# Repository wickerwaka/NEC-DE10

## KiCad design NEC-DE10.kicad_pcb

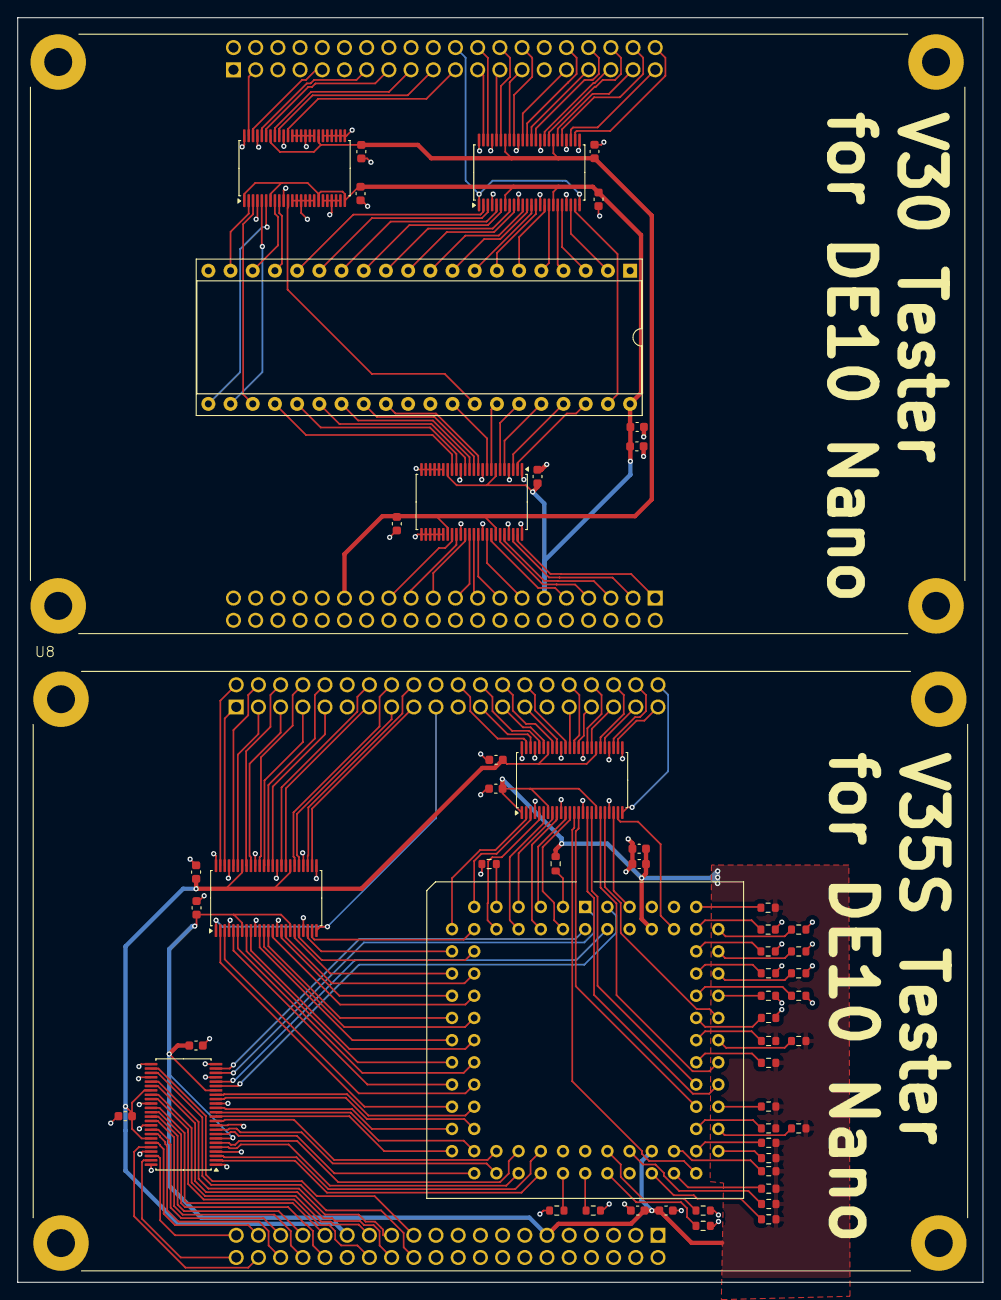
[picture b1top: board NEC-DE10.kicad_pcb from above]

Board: 2 copper layers, 110.4 x 144.7 mm, 56 parts (0 on the bottom side), 200 nets.

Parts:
C1, C2, C3, C4, C5, C6, C7, C8, C9, C10, C11, C12, C13, C14, C15: 100nF; C_0603_1608Metric
C16, C17, C18: 1uF; C_0603_1608Metric
R1, R2, R3, R4, R5, R6, R7, R8, R9, R10, R11, R12, R13, R14, R15, R16, R17, R18, R19, R20, R21, R22, R23, R24, R25, R26, R27, R28: 10k; R_0603_1608Metric
U1: DIP-40_W15.24mm_Socket
U2, U8: MODULE_P0496
U3, U4, U5, U6, U7, U10: 74ALVC164245; TSSOP-48_6.1x12.5mm_P0.5mm
U9: PLCC-84_THT-Socket

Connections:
+3.3V: C1.1, C2.1, C3.1, C8.1, C10.1, C12.1, U2.JP7_29 (3.3V_JP7), U3.31 (V_{CC(A)}), U3.42 (V_{CC(A)}), U4.31 (V_{CC(A)}), U4.42 (V_{CC(A)}), U5.31 (V_{CC(A)}), U5.42 (V_{CC(A)}), U6.31 (V_{CC(A)}), U6.42 (V_{CC(A)}), U7.31 (V_{CC(A)}), U7.42 (V_{CC(A)}), U8.JP7_29 (3.3V_JP7), U10.31 (V_{CC(A)}), U10.42 (V_{CC(A)})
+5V: C4.1, C5.1, C6.1, C7.1, C9.1, C11.1, C13.1, C14.1, C15.1, C16.1, C17.1, C18.1, R9.1, R10.1, R11.1, R12.1, R13.1, R14.1, R15.1, R16.1, R17.1, R18.1, R19.1, R25.1, R26.1, R27.1, U1.40 (VDD), U2.JP7_11 (5V_JP7), U3.7 (V_{CC(B)}), U3.18 (V_{CC(B)}), U4.7 (V_{CC(B)}), U4.18 (V_{CC(B)}), U5.1 (1DIR), U5.7 (V_{CC(B)}), U5.18 (V_{CC(B)}), U5.24 (2DIR), U6.7 (V_{CC(B)}), U6.18 (V_{CC(B)}), U7.7 (V_{CC(B)}), U7.18 (V_{CC(B)}), U8.JP7_11 (5V_JP7), U9.50 (VDD), U9.80 (VDD), U10.1 (1DIR), U10.7 (V_{CC(B)}), U10.18 (V_{CC(B)})
/V30/A16: U1.38 (A16/PS0), U4.2 (1B0)
/V30/A17: U1.37 (A17/PS1), U4.3 (1B1)
/V30/A18: U1.36 (A18/PS2), U4.5 (1B2)
/V30/A19: U1.35 (A19/PS3), U4.6 (1B3)
/V30/AD0: U1.16 (AD0), U3.2 (1B0)
/V30/AD1: U1.15 (AD1), U3.3 (1B1)
/V30/AD2: U1.14 (AD2), U3.5 (1B2)
/V30/AD3: U1.13 (AD3), U3.6 (1B3)
/V30/AD4: U1.12 (AD4), U3.8 (1B4)
/V30/AD5: U1.11 (AD5), U3.9 (1B5)
/V30/AD6: U1.10 (AD6), U3.11 (1B6)
/V30/AD7: U1.9 (AD7), U3.12 (1B7)
/V30/AD8: U1.8 (AD8), U3.13 (2B0)
/V30/AD9: U1.7 (AD9), U3.14 (2B1)
/V30/AD10: U1.6 (AD10), U3.16 (2B2)
/V30/AD11: U1.5 (AD11), U3.17 (2B3)
/V30/AD12: U1.4 (AD12), U3.19 (2B4)
/V30/AD13: U1.3 (AD13), U3.20 (2B5)
/V30/AD14: U1.2 (AD14), U3.22 (2B6)
/V30/AD15: U1.39 (AD15), U3.23 (2B7)
/V30/ASTB: U1.25 (ASTB), U4.16 (2B2)
/V30/BUF~R/W: U1.27 (BUF~R/W), U4.13 (2B0)
/V30/CLK: U1.19 (CLK), U5.2 (1B0)
/V30/F_A16: U2.JP7_1 (GPIO1_0), U4.47 (1A0)
/V30/F_A17: U2.JP7_3 (GPIO1_2), U4.46 (1A1)
/V30/F_A18: U2.JP7_5 (GPIO1_4), U4.44 (1A2)
/V30/F_A19: U2.JP7_7 (GPIO1_6), U4.43 (1A3)
/V30/F_AD0: U2.JP1_23 (GPIO0_20), U3.47 (1A0)
/V30/F_AD1: U2.JP1_24 (GPIO0_21), U3.46 (1A1)
/V30/F_AD2: U2.JP1_25 (GPIO0_22), U3.44 (1A2)
/V30/F_AD3: U2.JP1_26 (GPIO0_23), U3.43 (1A3)
/V30/F_AD4: U2.JP1_27 (GPIO0_24), U3.41 (1A4)
/V30/F_AD5: U2.JP1_28 (GPIO0_25), U3.40 (1A5)
/V30/F_AD6: U2.JP1_31 (GPIO0_26), U3.38 (1A6)
/V30/F_AD7: U2.JP1_32 (GPIO0_27), U3.37 (1A7)
/V30/F_AD8: U2.JP1_33 (GPIO0_28), U3.36 (2A0)
/V30/F_AD9: U2.JP1_34 (GPIO0_29), U3.35 (2A1)
/V30/F_AD10: U2.JP1_35 (GPIO0_30), U3.33 (2A2)
/V30/F_AD11: U2.JP1_36 (GPIO0_31), U3.32 (2A3)
/V30/F_AD12: U2.JP1_37 (GPIO0_32), U3.30 (2A4)
/V30/F_AD13: U2.JP1_38 (GPIO0_33), U3.29 (2A5)
/V30/F_AD14: U2.JP1_39 (GPIO0_34), U3.27 (2A6)
/V30/F_AD15: U2.JP1_40 (GPIO0_35), U3.26 (2A7)
/V30/F_AD_DIR: U2.JP1_22 (GPIO0_19), U3.1 (1DIR), U3.24 (2DIR)
/V30/F_ASTB: U2.JP7_23 (GPIO1_20), U4.33 (2A2)
/V30/F_BUF~R/W: U2.JP7_19 (GPIO1_16), U4.36 (2A0)
/V30/F_CLK: U2.JP1_3 (GPIO0_2), U5.47 (1A0)
/V30/F_INT: U2.JP1_17 (GPIO0_14), U5.41 (1A4)
/V30/F_NMI: U2.JP1_19 (GPIO0_16), U5.40 (1A5)
/V30/F_READY: U2.JP1_13 (GPIO0_10), U5.44 (1A2)
/V30/F_RESET: U2.JP1_15 (GPIO0_12), U5.43 (1A3)
/V30/F_S/~LG: U2.JP1_21 (GPIO0_18), U5.38 (1A6)
/V30/F_~BUFEN: U2.JP7_21 (GPIO1_18), U4.35 (2A1)
/V30/F_~INTAK: U2.JP7_25 (GPIO1_22), U4.32 (2A3)
/V30/F_~IO/M: U2.JP7_17 (GPIO1_14), U4.37 (1A7)
/V30/F_~POLL: U2.JP1_9 (GPIO0_8), U5.46 (1A1)
/V30/F_~RD: U2.JP7_13 (GPIO1_10), U4.40 (1A5)
/V30/F_~UBE: U2.JP7_9 (GPIO1_8), U4.41 (1A4)
/V30/F_~WR: U2.JP7_15 (GPIO1_12), U4.38 (1A6)
/V30/INT: U1.18 (INT), U5.8 (1B4)
/V30/NMI: U1.17 (NMI), U5.9 (1B5)
/V30/READY: U1.22 (READY), U5.5 (1B2)
/V30/RESET: U1.21 (RESET), U5.6 (1B3)
/V30/S/~LG: U1.33 (S/~LG), U5.11 (1B6)
/V30/~BUFEN: U1.26 (~BUFEN), U4.14 (2B1)
/V30/~INTAK: U1.24 (~INTAK), U4.17 (2B3)
/V30/~IO/M: U1.28 (~IO/M), U4.12 (1B7)
/V30/~POLL: U1.23 (~POLL), U5.3 (1B1)
/V30/~RD: U1.32 (~RD), U4.9 (1B5)
/V30/~UBE: U1.34 (~UBE), U4.8 (1B4)
/V30/~WR: U1.29 (~WR), U4.11 (1B6)
/V35/A0: U6.17 (2B3), U9.29 (A0)
/V35/A1: U6.14 (2B1), U9.30 (A9/A1)
/V35/A2: U6.16 (2B2), U9.31 (A10/A2)
/V35/A3: U6.12 (1B7), U9.32 (A11/A3)
/V35/A4: U6.8 (1B4), U9.33 (A12/A4)
/V35/A5: U6.13 (2B0), U9.34 (A13/A5)
/V35/A6: U6.9 (1B5), U9.35 (A14/A6)
/V35/A7: U6.11 (1B6), U9.36 (A15/A7)
/V35/A8: U6.5 (1B2), U9.37 (A16/A8)
/V35/A9: U6.6 (1B3), U9.38 (A17/A18)
/V35/A10: U6.2 (1B0), U9.39 (A19)
/V35/A11: U6.3 (1B1), U9.40 (A18/~UBE)
/V35/D0: U7.23 (2B7), U9.13 (D0)
/V35/D1: U7.22 (2B6), U9.14 (D1)
/V35/D2: U7.20 (2B5), U9.15 (D2)
/V35/D3: U7.19 (2B4), U9.16 (D3)
/V35/D4: U7.17 (2B3), U9.17 (D4)
/V35/D5: U7.16 (2B2), U9.18 (D5)
/V35/D6: U7.14 (2B1), U9.19 (D6)
/V35/D7: U7.13 (2B0), U9.20 (D7)
/V35/D8: U7.12 (1B7), U9.21 (D8)
/V35/D9: U7.11 (1B6), U9.22 (D9)
/V35/D10: U7.9 (1B5), U9.23 (D10)
/V35/D11: U7.8 (1B4), U9.24 (D11)
/V35/D12: U7.6 (1B3), U9.25 (D12)
/V35/D13: U7.5 (1B2), U9.26 (D13)
/V35/D14: U7.3 (1B1), U9.27 (D14)
/V35/D15: U7.2 (1B0), U9.28 (D15)
/V35/F_A0: U6.32 (2A3), U8.JP7_27 (GPIO1_24)
/V35/F_A1: U6.35 (2A1), U8.JP7_31 (GPIO1_26)
/V35/F_A2: U6.33 (2A2), U8.JP7_28 (GPIO1_25)
/V35/F_A3: U6.37 (1A7), U8.JP7_33 (GPIO1_28)
/V35/F_A4: U6.41 (1A4), U8.JP7_36 (GPIO1_31)
/V35/F_A5: U6.36 (2A0), U8.JP7_32 (GPIO1_27)
/V35/F_A6: U6.40 (1A5), U8.JP7_35 (GPIO1_30)
/V35/F_A7: U6.38 (1A6), U8.JP7_34 (GPIO1_29)
/V35/F_A8: U6.44 (1A2), U8.JP7_38 (GPIO1_33)
/V35/F_A9: U6.43 (1A3), U8.JP7_37 (GPIO1_32)
/V35/F_A10: U6.47 (1A0), U8.JP7_40 (GPIO1_35)
/V35/F_A11: U6.46 (1A1), U8.JP7_39 (GPIO1_34)
/V35/F_D0: U7.26 (2A7), U8.JP1_17 (GPIO0_14)
/V35/F_D1: U7.27 (2A6), U8.JP1_18 (GPIO0_15)
/V35/F_D2: U7.29 (2A5), U8.JP1_15 (GPIO0_12)
/V35/F_D3: U7.30 (2A4), U8.JP1_16 (GPIO0_13)
/V35/F_D4: U7.32 (2A3), U8.JP1_13 (GPIO0_10)
/V35/F_D5: U7.33 (2A2), U8.JP1_14 (GPIO0_11)
/V35/F_D6: U7.35 (2A1), U8.JP1_9 (GPIO0_8)
/V35/F_D7: U7.36 (2A0), U8.JP1_10 (GPIO0_9)
/V35/F_D8: U7.37 (1A7), U8.JP1_7 (GPIO0_6)
/V35/F_D9: U7.38 (1A6), U8.JP1_8 (GPIO0_7)
/V35/F_D10: U7.40 (1A5), U8.JP1_5 (GPIO0_4)
/V35/F_D11: U7.41 (1A4), U8.JP1_6 (GPIO0_5)
/V35/F_D12: U7.43 (1A3), U8.JP1_3 (GPIO0_2)
/V35/F_D13: U7.44 (1A2), U8.JP1_4 (GPIO0_3)
/V35/F_D14: U7.46 (1A1), U8.JP1_1 (GPIO0_0)
/V35/F_D15: U7.47 (1A0), U8.JP1_2 (GPIO0_1)
/V35/F_D_DIR: U7.1 (1DIR), U7.24 (2DIR), U8.JP1_19 (GPIO0_16)
/V35/F_NMI: U8.JP1_33 (GPIO0_28), U10.35 (2A1)
/V35/F_N/~S: U8.JP1_32 (GPIO0_27), U10.36 (2A0)
/V35/F_P00: U8.JP1_31 (GPIO0_26), U10.37 (1A7)
/V35/F_P01: U8.JP1_28 (GPIO0_25), U10.38 (1A6)
/V35/F_P02: U8.JP1_27 (GPIO0_24), U10.40 (1A5)
/V35/F_P03: U8.JP1_26 (GPIO0_23), U10.41 (1A4)
/V35/F_P04: U8.JP1_25 (GPIO0_22), U10.43 (1A3)
/V35/F_P05: U8.JP1_24 (GPIO0_21), U10.44 (1A2)
/V35/F_P06: U8.JP1_23 (GPIO0_20), U10.46 (1A1)
/V35/F_P07: U8.JP1_22 (GPIO0_19), U10.47 (1A0)
/V35/F_P_DIR: U8.JP1_40 (GPIO0_35), U10.24 (2DIR)
/V35/F_READY: U8.JP1_37 (GPIO0_32), U10.29 (2A5)
/V35/F_R/~W: U6.30 (2A4), U8.JP7_26 (GPIO1_23)
/V35/F_X1: U8.JP1_39 (GPIO0_34), U10.26 (2A7)
/V35/F_~INTP0: U8.JP1_34 (GPIO0_29), U10.33 (2A2)
/V35/F_~INTP1: U8.JP1_35 (GPIO0_30), U10.32 (2A3)
/V35/F_~INTP2: U8.JP1_36 (GPIO0_31), U10.30 (2A4)
/V35/F_~IOSTB: U6.27 (2A6), U8.JP7_24 (GPIO1_21)
/V35/F_~MREQ: U6.26 (2A7), U8.JP7_23 (GPIO1_20)
/V35/F_~MSTB: U6.29 (2A5), U8.JP7_25 (GPIO1_22)
/V35/F_~RESET: U8.JP1_38 (GPIO0_33), U10.27 (2A6)
/V35/NMI: U9.59 (P10/NMI), U10.14 (2B1)
/V35/N/~S: U9.53 (N/~S), U10.13 (2B0)
/V35/P00: U9.4 (P00), U10.12 (1B7)
/V35/P01: U9.5 (P01), U10.11 (1B6)
/V35/P02: U9.6 (P02), U10.9 (1B5)
/V35/P03: U9.7 (P03), U10.8 (1B4)
/V35/P04: U9.8 (P04), U10.6 (1B3)
/V35/P05: U9.10 (P05), U10.5 (1B2)
/V35/P06: U9.11 (P06), U10.3 (1B1)
/V35/P07: U9.12 (P07/CLKOUT), U10.2 (1B0)
/V35/READY: U9.66 (P17/READY), U10.20 (2B5)
/V35/R/~W: U6.19 (2B4), U9.83 (R/~W)
/V35/X1: U9.78 (X1), U10.23 (2B7)
/V35/~INTP0: U9.60 (P11/~INTP0), U10.16 (2B2)
/V35/~INTP1: U9.61 (P12/~INTP1), U10.17 (2B3)
/V35/~INTP2: U9.62 (P13/~INTP2), U10.19 (2B4)
/V35/~IOSTB: U6.22 (2B6), U9.1 (~IOSTB)
/V35/~MREQ: U6.23 (2B7), U9.2 (~MREQ)
/V35/~MSTB: U6.20 (2B5), U9.84 (~MSTB)
/V35/~RESET: U9.81 (~RESET), U10.22 (2B6)
GND: C1.2, C2.2, C3.2, C4.2, C5.2, C6.2, C7.2, C8.2, C9.2, C10.2, C11.2, C12.2, C13.2, C14.2, C15.2, C16.2, C17.2, C18.2, R1.1, R2.1, R3.1, R4.1, R5.1, R6.1, R7.1, R8.1, R20.1, R21.1, R22.1, R23.1, R24.1, R28.1, U1.1 (IC), U1.20 (GND), U1.30 (HLDAK), U1.31 (HLDRQ), U2.JP1_12 (GND_JP1_12), U2.JP1_30 (GND_JP1_30), U2.JP7_12 (GND_JP7_12), U2.JP7_30 (GND_JP7_30), U2.SH1 (GND), U2.SH2 (GND), U2.SH3 (GND), U2.SH4 (GND), U3.4 (GND), U3.10 (GND), U3.15 (GND), U3.21 (GND), U3.25 (2~OE), U3.28 (GND), U3.34 (GND), U3.39 (GND), U3.45 (GND), U3.48 (1~OE), U4.1 (1DIR), U4.4 (GND), U4.10 (GND), U4.15 (GND), U4.19 (2B4), U4.20 (2B5), U4.21 (GND), U4.22 (2B6), U4.23 (2B7), U4.24 (2DIR), U4.25 (2~OE), U4.26 (2A7), U4.27 (2A6), U4.28 (GND), U4.29 (2A5), U4.30 (2A4), U4.34 (GND), U4.39 (GND), U4.45 (GND), U4.48 (1~OE), U5.4 (GND), U5.10 (GND), U5.12 (1B7), U5.13 (2B0), U5.14 (2B1), U5.15 (GND), U5.16 (2B2), U5.17 (2B3), U5.19 (2B4), U5.20 (2B5), U5.21 (GND), U5.22 (2B6), U5.23 (2B7), U5.25 (2~OE), U5.26 (2A7), U5.27 (2A6), U5.28 (GND), U5.29 (2A5), U5.30 (2A4), U5.32 (2A3), U5.33 (2A2), U5.34 (GND), U5.35 (2A1), U5.36 (2A0), U5.37 (1A7), U5.39 (GND), U5.45 (GND), U5.48 (1~OE), U6.1 (1DIR), U6.4 (GND), U6.10 (GND), U6.15 (GND), U6.21 (GND), U6.24 (2DIR), U6.25 (2~OE), U6.28 (GND), U6.34 (GND), U6.39 (GND), U6.45 (GND), U6.48 (1~OE), U7.4 (GND), U7.10 (GND), U7.15 (GND), U7.21 (GND), U7.25 (2~OE), U7.28 (GND), U7.34 (GND), U7.39 (GND), U7.45 (GND), U7.48 (1~OE), U8.JP1_12 (GND_JP1_12), U8.JP1_30 (GND_JP1_30), U8.JP7_12 (GND_JP7_12), U8.JP7_30 (GND_JP7_30), U8.SH1 (GND), U8.SH2 (GND), U8.SH3 (GND), U8.SH4 (GND), U9.42 (GND), U9.77 (GND), U10.4 (GND), U10.10 (GND), U10.15 (GND), U10.21 (GND), U10.25 (2~OE), U10.28 (GND), U10.34 (GND), U10.39 (GND), U10.45 (GND), U10.48 (1~OE)
unnamed: R25.2, U9.3 (IC)
unnamed: R26.2, U9.49 (IC)
unnamed: R27.2, U9.75 (IC)
unnamed: R17.2, U9.63 (P14/INT/~POLL)
unnamed: R18.2, U9.64 (P15/TOUT)
unnamed: R19.2, U9.65 (P16/~SCKO)
unnamed: R9.2, U9.48 (P20/~DMARQ0)
unnamed: R10.2, U9.51 (P21/~DMAAK0)
unnamed: R11.2, U9.52 (P22/~TC0)
unnamed: R12.2, U9.54 (P23/DMARQ1)
unnamed: R13.2, U9.55 (P24/~DMAAK1)
unnamed: R14.2, U9.56 (P25/~TC1)
unnamed: R15.2, U9.57 (P26/~HLDAK)
unnamed: R16.2, U9.58 (P27/~HLDRQ)
unnamed: R1.2, U9.67 (PT0)
unnamed: R2.2, U9.68 (PT1)
unnamed: R3.2, U9.69 (PT2)
unnamed: R4.2, U9.70 (PT3)
unnamed: R5.2, U9.71 (PT4)
unnamed: R6.2, U9.72 (PT5)
unnamed: R7.2, U9.73 (PT6)
unnamed: R8.2, U9.74 (PT7)
unnamed: R20.2, U9.41 (RxD0)
unnamed: R22.2, U9.45 (RxD1)
unnamed: R21.2, U9.43 (~CTS0)
unnamed: R23.2, U9.46 (~CTS1)
unnamed: R28.2, U9.9 (NOTE1)
unnamed: R24.2, U9.76 (VTH)

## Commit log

2025-01-18 V30 board done
2025-01-19 Added V35 board
2025-01-19 Fab changes
2025-01-19 Added STEP file
2025-01-20 Power tweaks. Revision 1 production submitted
2025-02-22 Adding power control Moving board around for heat issues
